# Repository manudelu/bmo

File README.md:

BMO - Adventure Time AI Agent
=============================

Electronics
------------------------

* Raspberry Pi 5 (w/ active cooler)
* Freenove 5 inch touchscreen monitor
* Camera Module 3 Wide NoIR

Future Additions
------------------

* USB microphone
* Speaker
* Custom PCB for button control (using Raspberry Pi 5 GPIO)
* Raspberry Pi AI HAT+ 2 (Hailo-10H AI accelerator and 8GB of on‑board RAM)

Setup
------------

Target: Raspberry Pi 5 with 8 GB RAM and Raspberry Pi OS 64-bit.

```bash
git clone --recurse-submodules <repository-url> bmo
cd bmo
./setup.sh
```

For an existing checkout, just run `./setup.sh`. It:

- Creates or reuses `.venv/` using the system `python3`.
- Installs the Python dependencies in `requirements.txt`.
- Builds `third_party/whisper.cpp` for the current machine.
- Downloads the Whisper model and Piper voice selected in `config/agent.yaml` if missing.
- Installs Ollama if needed and downloads the model in `config/agent.yaml`.

If Ollama is not running and no systemd service is available, start
`ollama serve` in another terminal and rerun setup.

Models and configuration
------------

Edit `config/agent.yaml` to select both the assistant and speech models. Both setup and the application read this file. After changing a model or voice, rerun `./setup.sh` to download it, then restart BMO.

The `ollama` section controls the assistant model, prompt, and generation settings.

Run BMO
------------

```bash
.venv/bin/python src/fsm.py
```

Focus the BMO window and press Space. Begin speaking within five seconds,
then pause to finish your question. BMO stops after 900 ms of silence or at
the 15-second limit. Silent input is skipped. BMO transcribes with Whisper,
asks Ollama, generates speech with Piper,
and returns to idle after playback. Escape, Q, or closing the window exits.
Recording and inference run in workers so face animations remain responsive.

On the Pi, `arecord` and `aplay` use the default ALSA devices. To select a
microphone, find its card/device with `arecord -l`, then use, for example:

```bash
BMO_CAPTURE_DEVICE=plughw:2,0 .venv/bin/python src/fsm.py
```

Replace `2,0` with your microphone's actual card and device numbers.
`BMO_PLAYER` selects the playback executable; playback uses that player's
default output device.

Upstream documentation:
[Whisper](https://github.com/ggml-org/whisper.cpp),
[Piper](https://github.com/OHF-Voice/piper1-gpl),
[Ollama Linux setup](https://docs.ollama.com/linux).

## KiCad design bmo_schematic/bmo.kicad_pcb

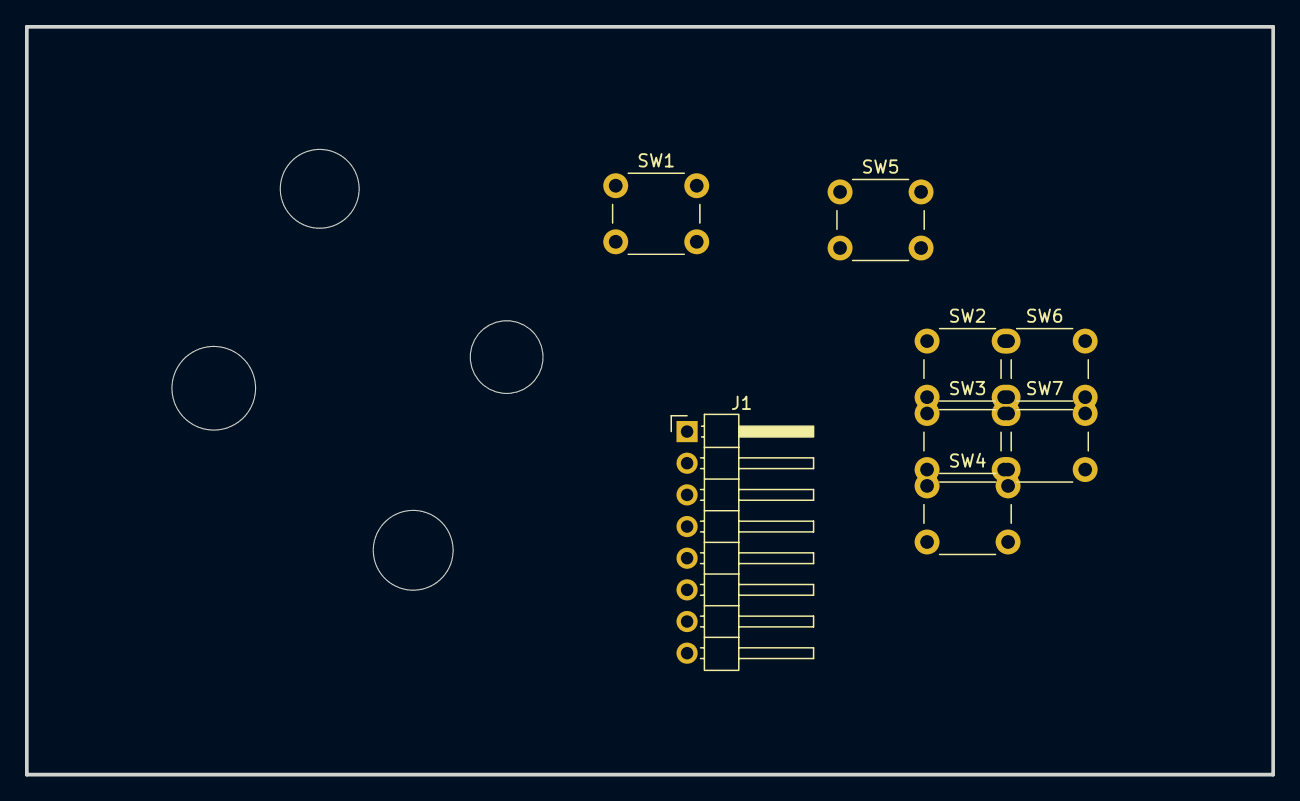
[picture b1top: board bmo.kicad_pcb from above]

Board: 2 copper layers, 100.0 x 60.0 mm, 8 parts (0 on the bottom side), 8 nets, no tracks yet.

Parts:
J1: Conn_01x08; PinHeader_1x08_P2.54mm_Horizontal
SW1, SW2, SW3, SW4, SW5, SW6, SW7: SW_Push; SW_PUSH_6mm_H4.3mm

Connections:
GND: J1.8, SW1.1, SW2.1, SW3.1, SW4.1, SW5.1, SW6.1, SW7.1
unnamed: J1.1, SW1.2
unnamed: J1.2, SW2.2
unnamed: J1.3, SW3.2
unnamed: J1.4, SW4.2
unnamed: J1.5, SW5.2
unnamed: J1.6, SW6.2
unnamed: J1.7, SW7.2
